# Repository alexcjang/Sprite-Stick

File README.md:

# Sprite-Stick
MicroSD-Driven Mini USB Display Engine built on RP2040 and USB2642

Sprite Stick is an ultra-compact, high-speed custom USB peripheral engineered to dynamically drive a tiny onboard display while serving as a USB mass storage device. Designed as a sleek, self-contained 4-layer PCB, the hardware combines a high-speed USB 2.0 Hub Controller (USB2642), a Waveshare RP2040-Zero micro-controller, a MicroSD card interface, and an integrated SPI display engine.

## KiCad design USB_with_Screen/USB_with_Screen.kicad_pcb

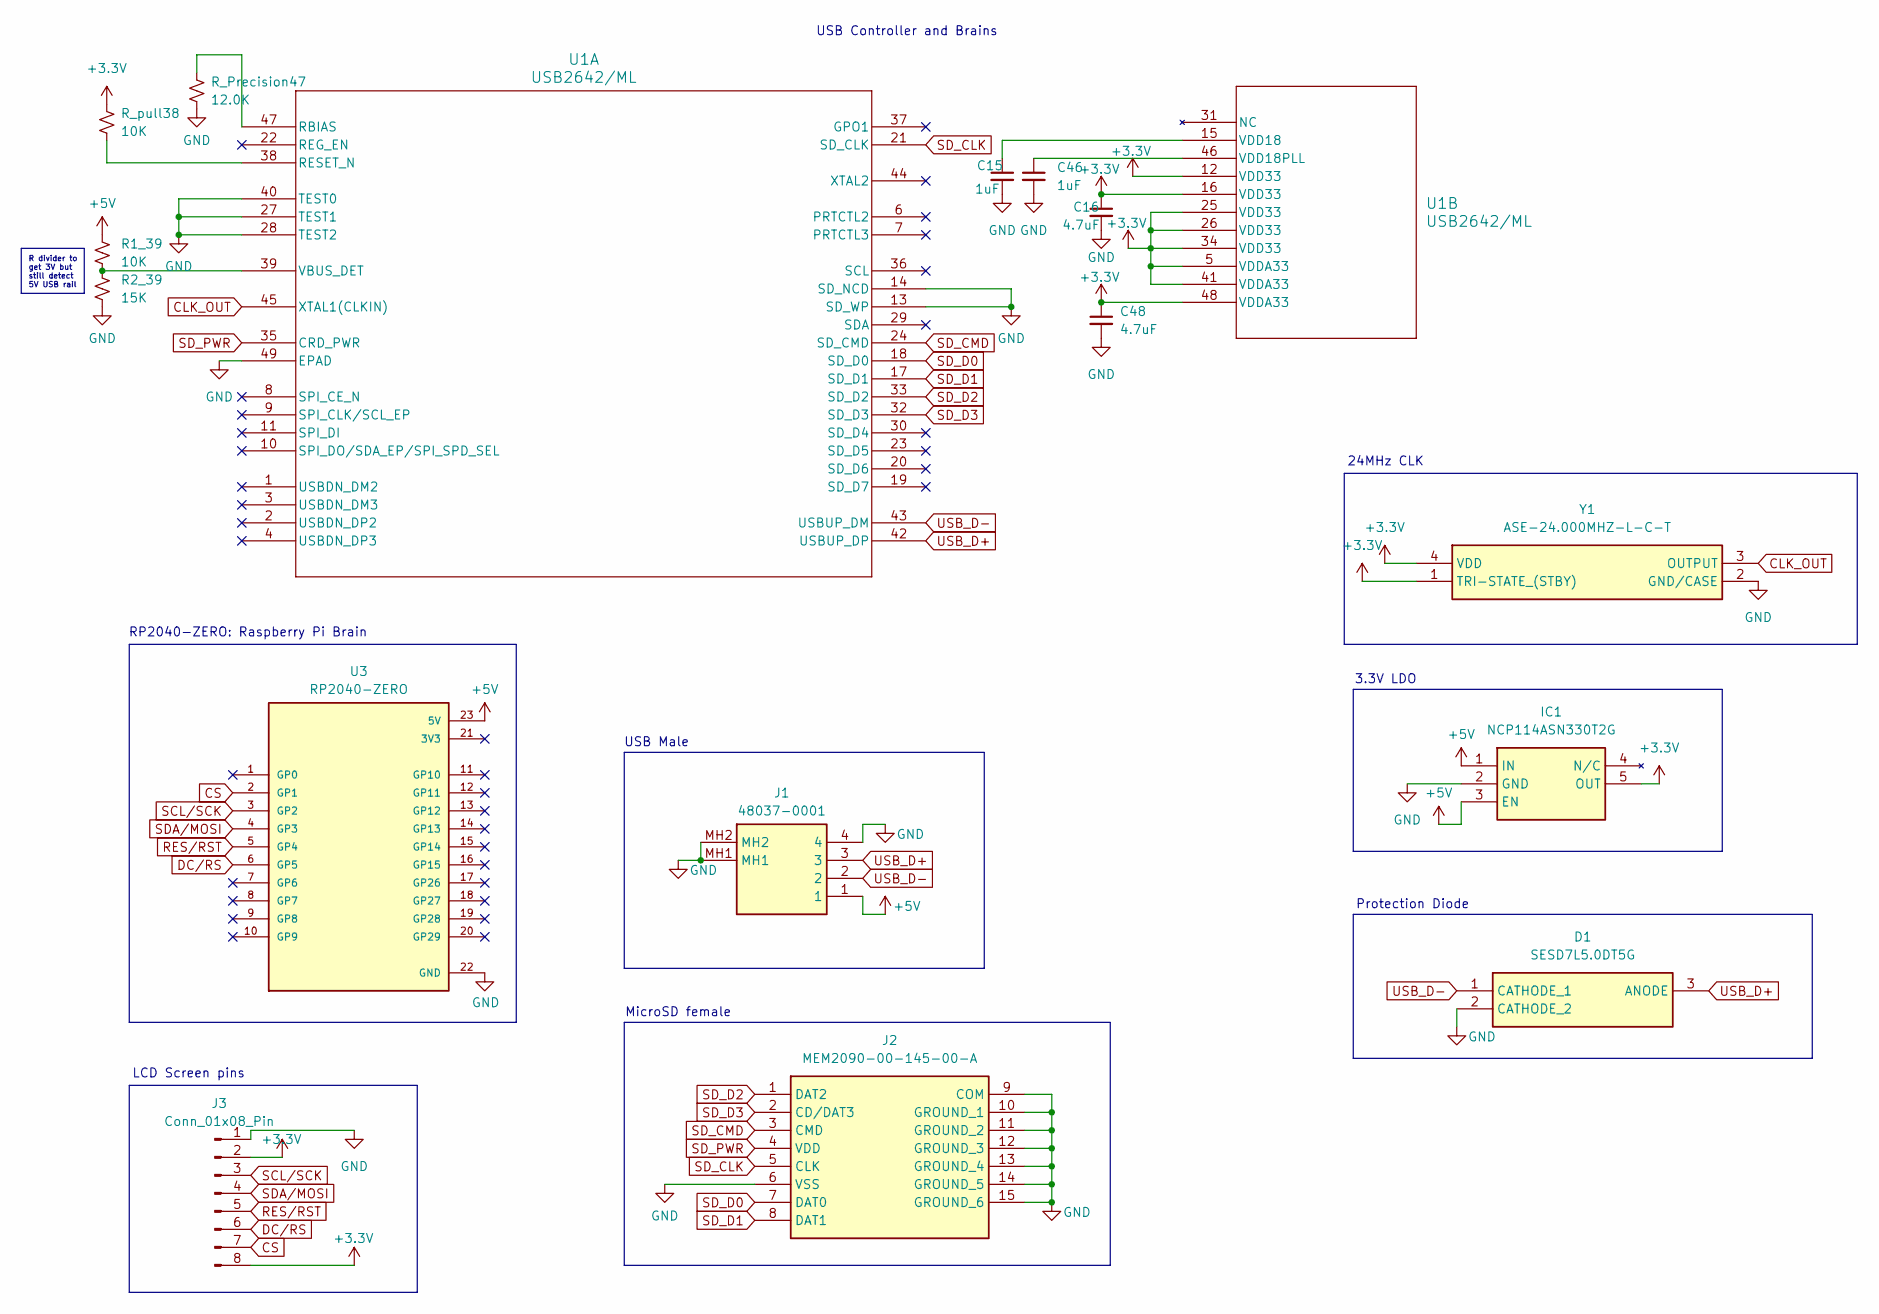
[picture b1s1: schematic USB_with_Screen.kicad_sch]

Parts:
C15, C46: 1uF; C_0805_2012Metric_Pad1.18x1.45mm_HandSolder
C16, C48: 4.7uF; C_0805_2012Metric_Pad1.18x1.45mm_HandSolder
D1: SESD7L5.0DT5G; SOTFL40P120X55-3N; Mouser Part Number 863-SESD7L5.0DT5G
IC1: NCP114ASN330T2G; SOT95P275X110-5N; Mouser Part Number 863-NCP114ASN330T2G
J1: 48037-0001; 480370001; Mouser Part Number 538-48037-0001
J2: MEM2090-00-145-00-A; MEM20900014500A; Mouser Part Number 640-MEM20900014500A
J3: Conn_01x08_Pin; PinHeader_1x08_P2.54mm_Vertical
R1_39: 10K; R_0805_2012Metric_Pad1.20x1.40mm_HandSolder
R2_39: 15K; R_0805_2012Metric_Pad1.20x1.40mm_HandSolder
R_Precision47: 12.0K; R_0805_2012Metric_Pad1.20x1.40mm_HandSolder
R_pull38: 10K; R_0805_2012Metric_Pad1.20x1.40mm_HandSolder
U1: USB2642/ML; QFN48_7X7MC_MCH
U3: RP2040-ZERO; MODULE_RP2040-ZERO; PARTREV NA
Y1: ASE-24.000MHZ-L-C-T; ASE24576MHZLCT; Mouser Part Number 815-ASE-24.000MLCT

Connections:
+3.3V: C16.1, C48.1, IC1.5 (OUT), J3.2, J3.8, R_pull38.1, U1.5 (VDDA33), U1.12 (VDD33), U1.16 (VDD33), U1.25 (VDD33), U1.26 (VDD33), U1.34 (VDD33), U1.41 (VDDA33), U1.48 (VDDA33), Y1.1 (TRI-STATE_(STBY)), Y1.4 (VDD)
+5V: IC1.1 (IN), IC1.3 (EN), J1.1, R1_39.1, U3.23 (5V)
CLK_OUT: U1.45 (XTAL1(CLKIN)), Y1.3 (OUTPUT)
CS: J3.7, U3.2 (GP1)
DC/RS: J3.6, U3.6 (GP5)
GND: C15.2, C16.2, C46.2, C48.2, D1.2 (CATHODE_2), IC1.2 (GND), J1.4, J1.MH1, J1.MH2, J2.6 (VSS), J2.9 (COM), J2.10 (GROUND_1), J2.11 (GROUND_2), J2.12 (GROUND_3), J2.13 (GROUND_4), J2.14 (GROUND_5), J2.15 (GROUND_6), J3.1, R2_39.2, R_Precision47.2, U1.13 (SD_WP), U1.14 (SD_NCD), U1.27 (TEST1), U1.28 (TEST2), U1.40 (TEST0), U1.49 (EPAD), U3.22 (GND), Y1.2 (GND/CASE)
unnamed: R_Precision47.1, U1.47 (RBIAS)
unnamed: R_pull38.2, U1.38 (RESET_N)
unnamed: R1_39.2, R2_39.1, U1.39 (VBUS_DET)
unnamed: C15.1, U1.15 (VDD18)
unnamed: C46.1, U1.46 (VDD18PLL)
RES/RST: J3.5, U3.5 (GP4)
SCL/SCK: J3.3, U3.3 (GP2)
SDA/MOSI: J3.4, U3.4 (GP3)
SD_CLK: J2.5 (CLK), U1.21 (SD_CLK)
SD_CMD: J2.3 (CMD), U1.24 (SD_CMD)
SD_D0: J2.7 (DAT0), U1.18 (SD_D0)
SD_D1: J2.8 (DAT1), U1.17 (SD_D1)
SD_D2: J2.1 (DAT2), U1.33 (SD_D2)
SD_D3: J2.2 (CD/DAT3), U1.32 (SD_D3)
SD_PWR: J2.4 (VDD), U1.35 (CRD_PWR)
USB_D+: D1.3 (ANODE), J1.3, U1.42 (USBUP_DP)
USB_D-: D1.1 (CATHODE_1), J1.2, U1.43 (USBUP_DM)

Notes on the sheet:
USB Male
LCD Screen pins
Protection Diode
3.3V LDO
USB Controller and Brains
MicroSD female
24MHz CLK
RP2040-ZERO: Raspberry Pi Brain
R divider to get 3V but still detect 5V USB rail

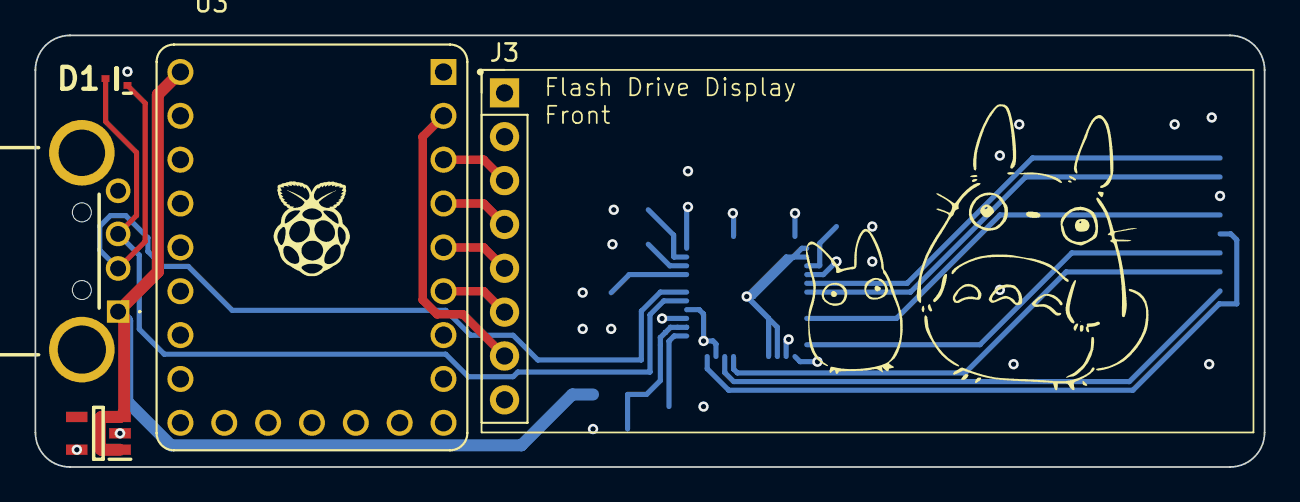
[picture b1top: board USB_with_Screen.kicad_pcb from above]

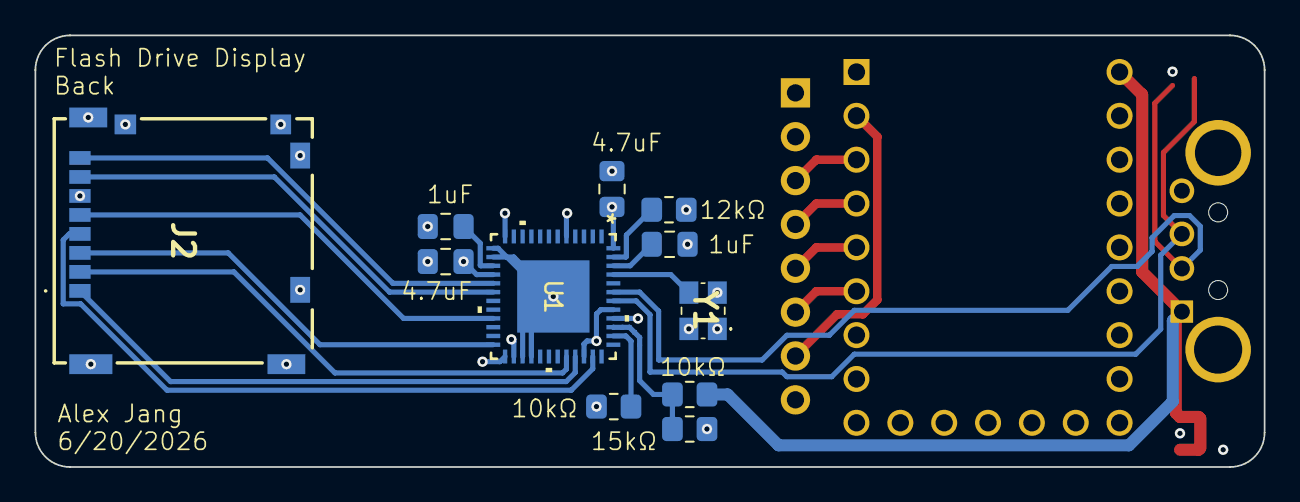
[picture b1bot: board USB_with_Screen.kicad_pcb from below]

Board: 4 copper layers, 71.2 x 25.0 mm, 16 parts (11 on the bottom side), 23 nets.
